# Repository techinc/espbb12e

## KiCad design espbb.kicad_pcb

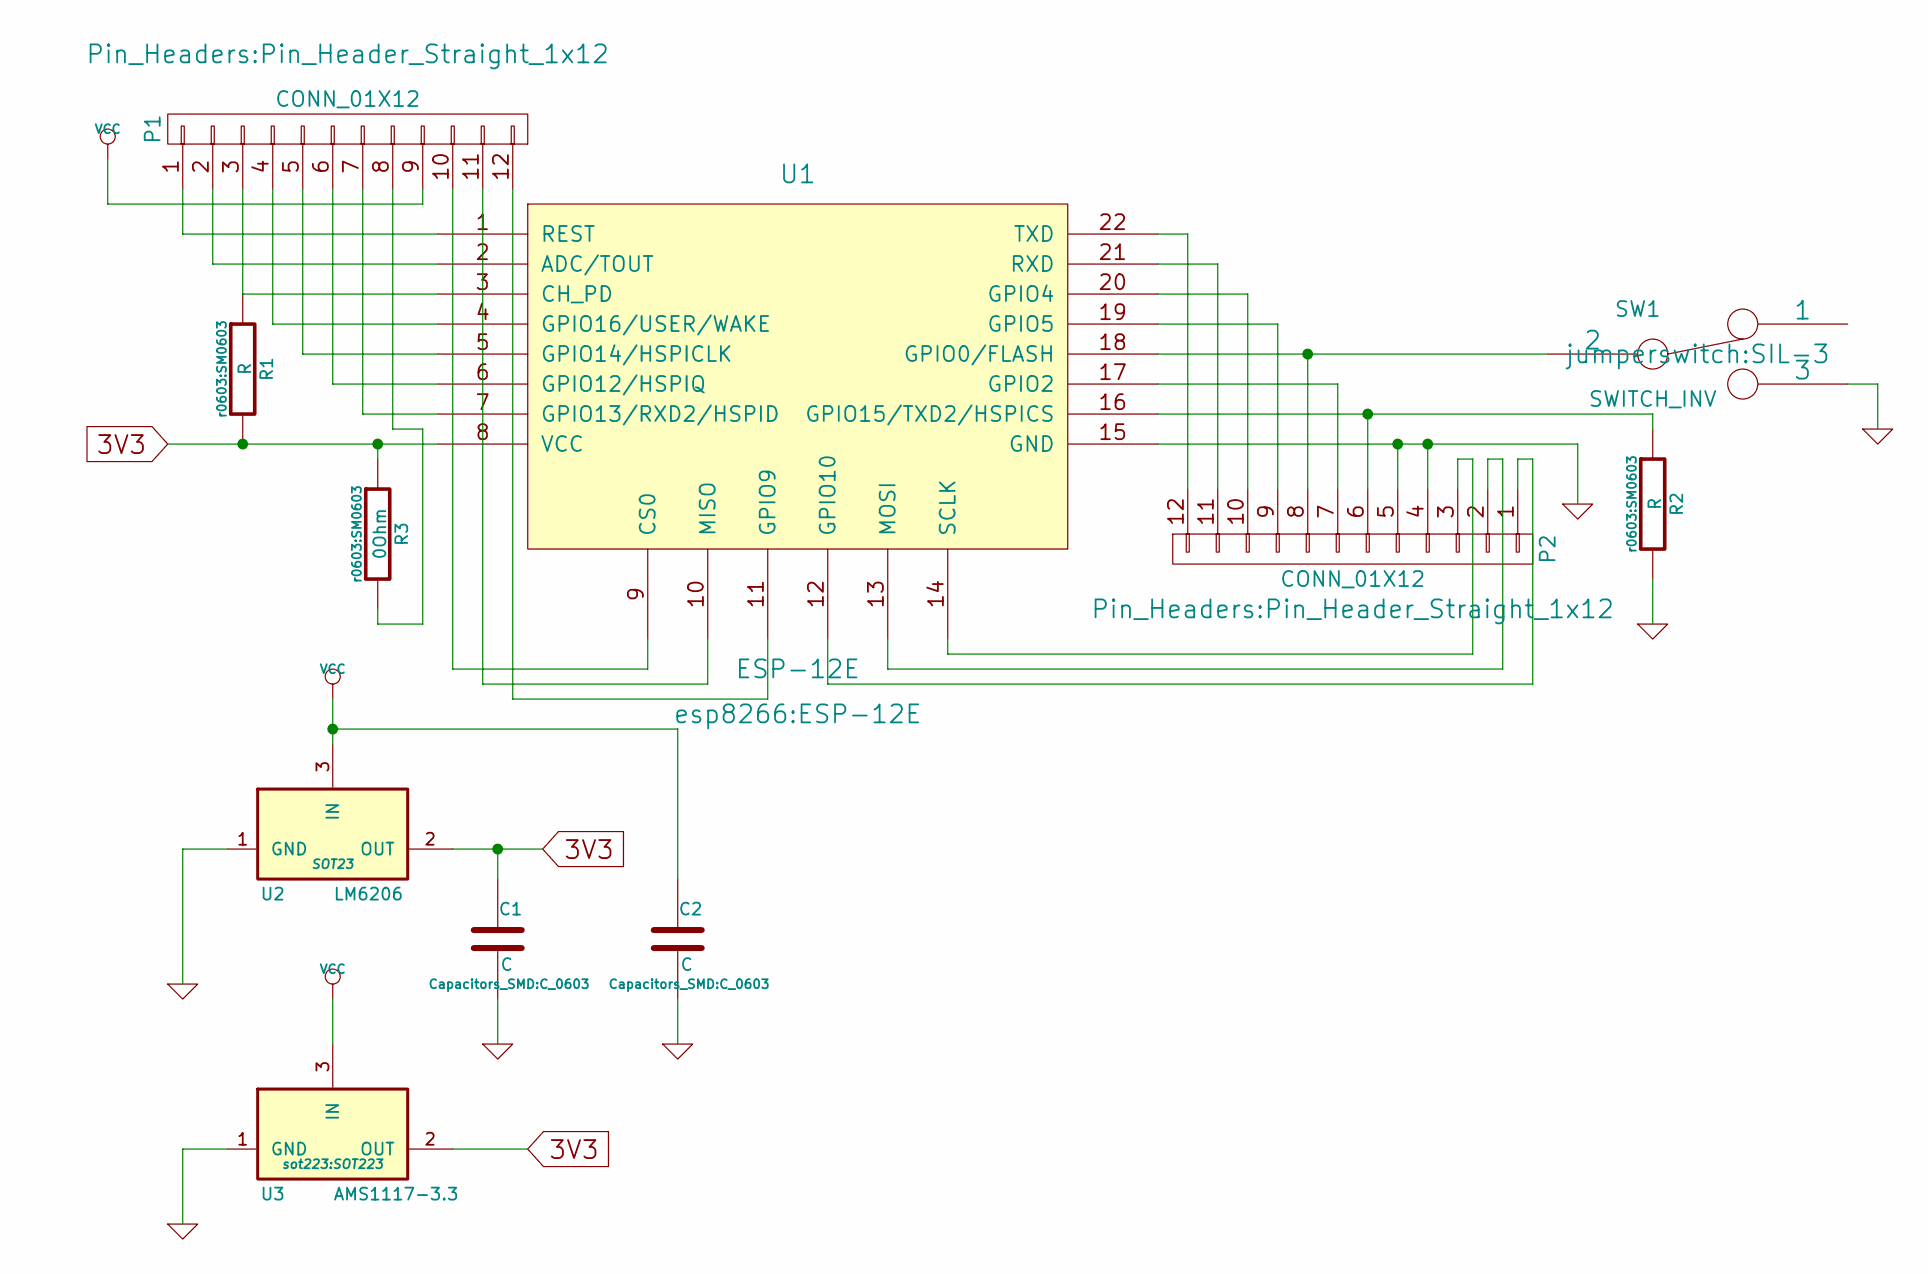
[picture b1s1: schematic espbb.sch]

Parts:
C1, C2: C; C_0603
P1, P2: CONN_01X12; Pin_Header_Straight_1x12
R1, R2: R; SM0603
R3: 0Ohm; SM0603
SW1: SWITCH_INV; SIL-3
U1: ESP-12E
U2: LM6206; SOT23
U3: AMS1117-3.3; SOT223

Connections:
3V3: C1.1, R1.2, R3.1, U1.8 (VCC), U2.2 (OUT), U3.2 (OUT)
GND: C1.2, C2.2, P2.4, P2.5, R2.2, SW1.3, U1.15 (GND), U2.1 (GND), U3.1 (GND)
unnamed: P1.1, U1.1 (REST)
unnamed: P1.2, U1.2 (ADC/TOUT)
unnamed: P1.3, R1.1, U1.3 (CH_PD)
unnamed: P1.4, U1.4 (GPIO16/USER/WAKE)
unnamed: P1.5, U1.5 (GPIO14/HSPICLK)
unnamed: P1.6, U1.6 (GPIO12/HSPIQ)
unnamed: P1.7, U1.7 (GPIO13/RXD2/HSPID)
unnamed: P1.8, R3.2
unnamed: P1.10, U1.9 (CS0)
unnamed: P1.11, U1.10 (MISO)
unnamed: P1.12, U1.11 (GPIO9)
unnamed: P2.1, U1.12 (GPIO10)
unnamed: P2.2, U1.13 (MOSI)
unnamed: P2.3, U1.14 (SCLK)
unnamed: P2.6, R2.1, U1.16 (GPIO15/TXD2/HSPICS)
unnamed: P2.7, U1.17 (GPIO2)
unnamed: P2.8, SW1.2, U1.18 (GPIO0/FLASH)
unnamed: P2.9, U1.19 (GPIO5)
unnamed: P2.10, U1.20 (GPIO4)
unnamed: P2.11, U1.21 (RXD)
unnamed: P2.12, U1.22 (TXD)
VCC: C2.1, P1.9, U2.3 (IN), U3.3 (IN)

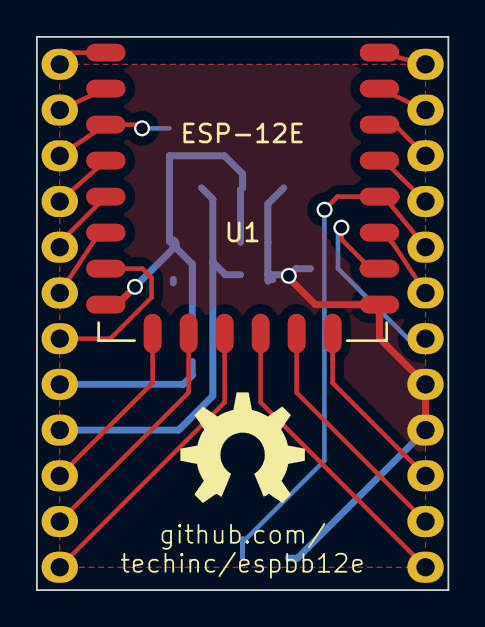
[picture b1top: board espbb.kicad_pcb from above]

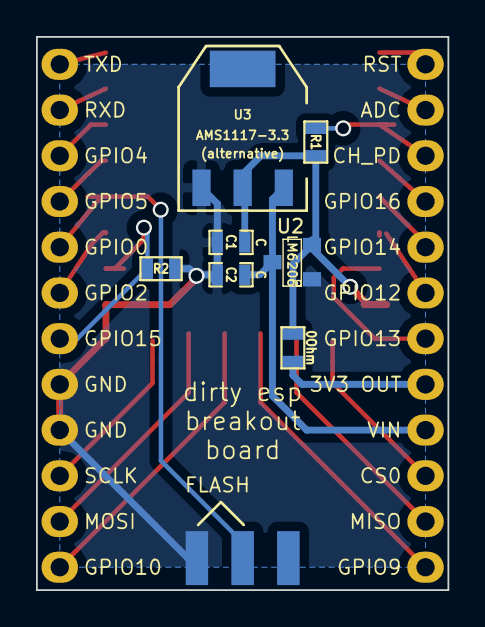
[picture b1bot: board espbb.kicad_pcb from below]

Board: 2 copper layers, 22.9 x 30.7 mm, 11 parts (8 on the bottom side), 24 nets.

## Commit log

2015-12-04 esp-12e version
2015-12-04 add correct gerbers
